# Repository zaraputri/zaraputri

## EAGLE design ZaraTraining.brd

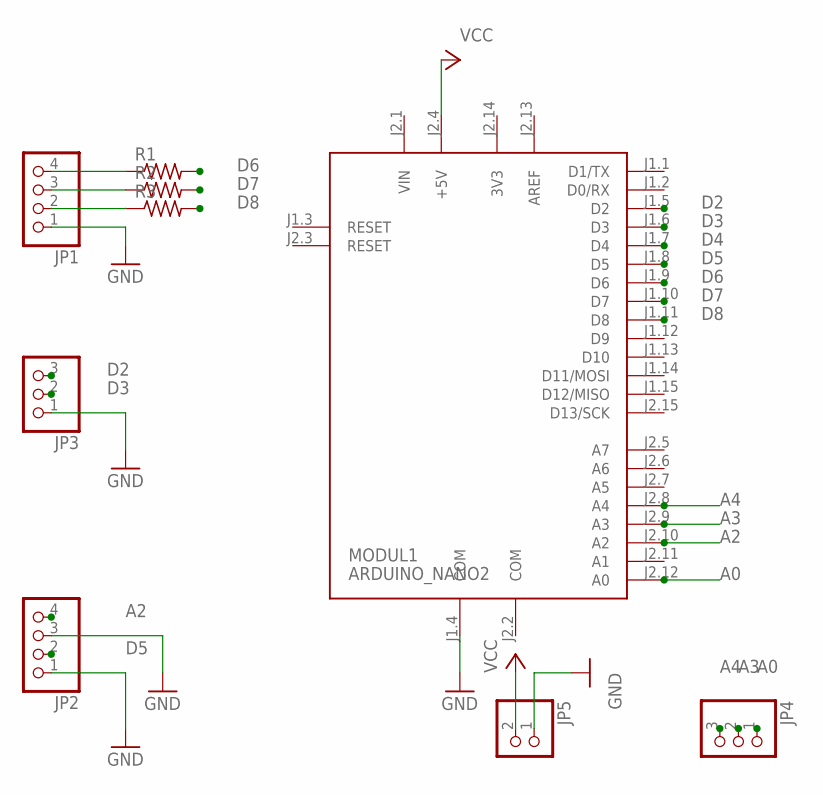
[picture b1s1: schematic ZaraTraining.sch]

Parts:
JP1, JP2: PINHD-1X4; 1X04
JP3, JP4: PINHD-1X3; 1X03
JP5: PINHD-1X2; 1X02
MODUL1: ARDUINO_NANO2
R1, R2, R3: R-US_0204/5; 0204/5

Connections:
3V3: MODUL1.J2.14 (3V3)
A0: JP4.1, MODUL1.J2.12 (A0)
A2: JP2.4, MODUL1.J2.10 (A2)
A3: JP4.2, MODUL1.J2.9 (A3)
A4: JP4.3, MODUL1.J2.8 (A4)
AREF: MODUL1.J2.13 (AREF)
COM: MODUL1.J2.2 (COM)
D2: JP3.3, MODUL1.J1.5 (D2)
D3: JP3.2, MODUL1.J1.6 (D3)
D4: MODUL1.J1.7 (D4)
D5: JP2.2, MODUL1.J1.8 (D5)
D6: MODUL1.J1.9 (D6), R1.2
D7: MODUL1.J1.10 (D7), R2.2
D8: MODUL1.J1.11 (D8), R3.2
GND: JP1.1, JP2.1, JP2.3, JP3.1, JP5.1, MODUL1.J1.4 (COM)
unnamed: JP1.4, R1.1
unnamed: JP1.3, R2.1
unnamed: JP1.2, R3.1
VCC: JP5.2, MODUL1.J2.4 (+5V)
VIN: MODUL1.J2.1 (VIN)

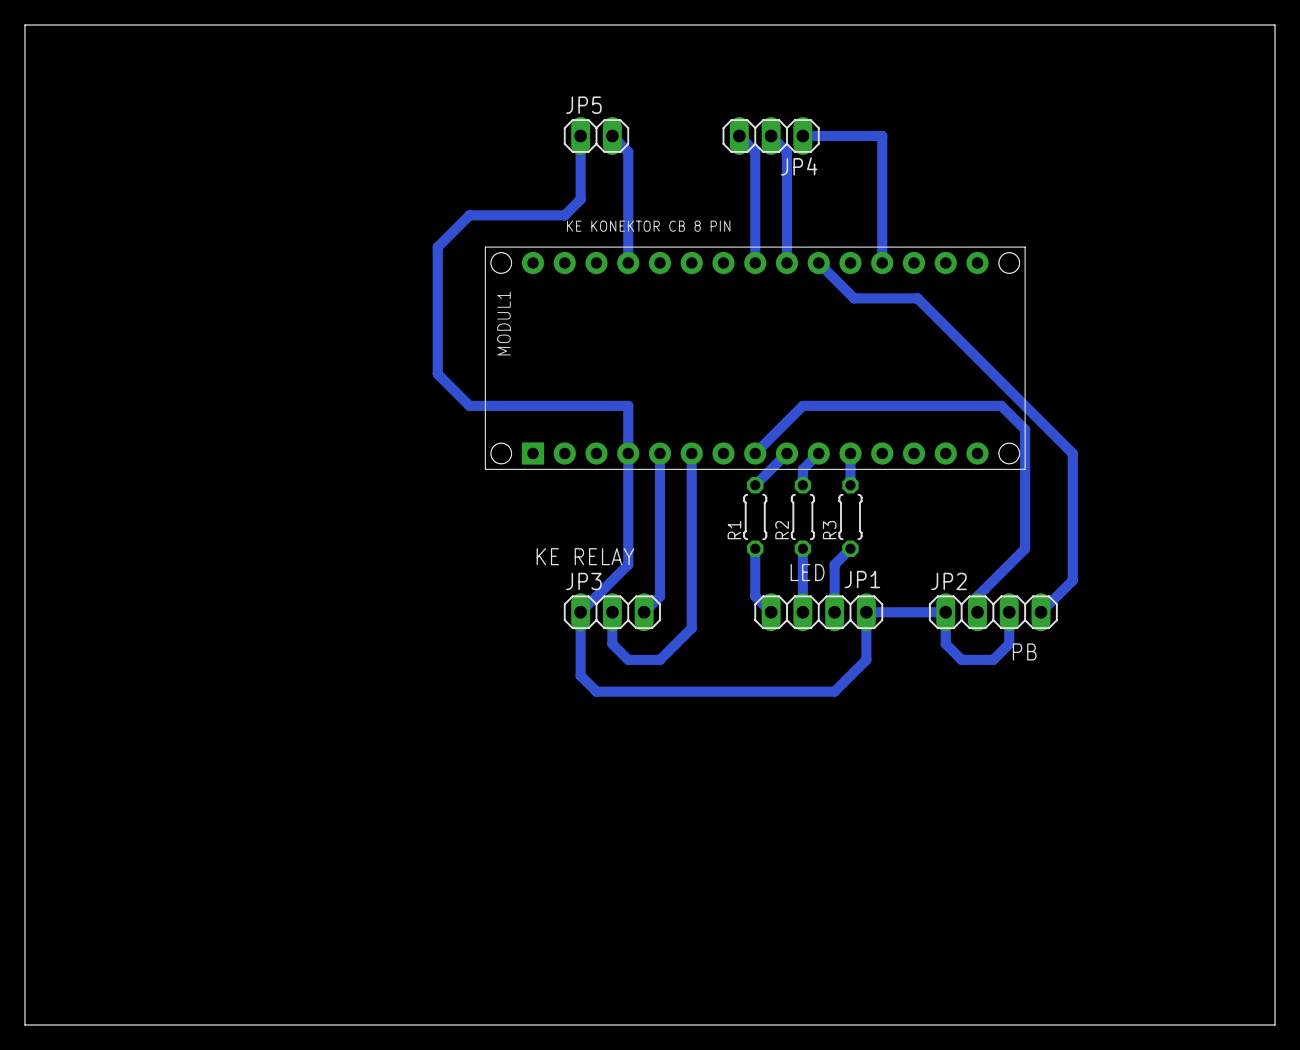
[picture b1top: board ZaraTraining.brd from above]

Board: 2 copper layers, 100.0 x 80.0 mm, 9 parts (0 on the bottom side), 15 nets.
